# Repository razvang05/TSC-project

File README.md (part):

# TSC-project

**Author: Razvan Gheorghe 334CA**

## • Diagrama Bloc

## • BOM (Bill of Materials)

**Note:** TP-urile au fost construite de mine.

  | Nr. | Component Name | Procurement Link | Datasheet Link |
  |-----|----------------|------------------|----------------|
  | 1 | BOOT_BUTON | [Link](https://www.snapeda.com/parts/EVQP7L01P/Panasonic%20Electronic%20Components/view-part/?welcome=home) | [Datasheet](https://www.snapeda.com/parts/EVQP7L01P/Panasonic/datasheet/) |
  | 2 | C1 | [Link](https://componentsearchengine.com/part-view/CC0402MRX5R5BB106/YAGEO) | [Datasheet](https://componentsearchengine.com/Datasheets/2/CC0402MRX5R5BB106.pdf) |
  | 3 | C1_BAT | [Link](https://componentsearchengine.com/part-view/CC0402MRX5R5BB106/YAGEO) | [Datasheet](https://componentsearchengine.com/Datasheets/2/CC0402MRX5R5BB106.pdf) |
  | 4 | C1_BAT2 | [Link](https://componentsearchengine.com/part-view/CC0402MRX5R5BB106/YAGEO) | [Datasheet](https://componentsearchengine.com/Datasheets/2/CC0402MRX5R5BB106.pdf) |
  | 5 | C2 | [Link](https://componentsearchengine.com/part-view/CC0402MRX5R5BB106/YAGEO) | [Datasheet](https://componentsearchengine.com/Datasheets/2/CC0402MRX5R5BB106.pdf) |
  | 6 | C2_BAT | [Link](https://componentsearchengine.com/part-view/CC0402MRX5R5BB106/YAGEO) | [Datasheet](https://componentsearchengine.com/Datasheets/2/CC0402MRX5R5BB106.pdf) |
  | 7 | C3 | [Link](https://componentsearchengine.com/part-view/CC0402MRX5R5BB106/YAGEO) | [Datasheet](https://componentsearchengine.com/Datasheets/2/CC0402MRX5R5BB106.pdf) |
  | 8 | C4 | [Link](https://componentsearchengine.com/part-view/CC0402MRX5R5BB106/YAGEO) | [Datasheet](https://componentsearchengine.com/Datasheets/2/CC0402MRX5R5BB106.pdf) |
  | 9 | C4_USB | [Link](https://componentsearchengine.com/part-view/CC0402MRX5R5BB106/YAGEO) | [Datasheet](https://componentsearchengine.com/Datasheets/2/CC0402MRX5R5BB106.pdf) |
  | 10 | C5 | [Link](https://componentsearchengine.com/part-view/CC0402MRX5R5BB106/YAGEO) | [Datasheet](https://componentsearchengine.com/Datasheets/2/CC0402MRX5R5BB106.pdf) |
  | 11 | C5_USB | [Link](https://componentsearchengine.com/part-view/CC0402MRX5R5BB106/YAGEO) | [Datasheet](https://componentsearchengine.com/Datasheets/2/CC0402MRX5R5BB106.pdf) |
  | 12 | C6 | [Link](https://componentsearchengine.com/part-view/CC0402MRX5R5BB106/YAGEO) | [Datasheet](https://componentsearchengine.com/Datasheets/2/CC0402MRX5R5BB106.pdf) |
  | 13 | C7 | [Link](https://componentsearchengine.com/part-view/CC0402MRX5R5BB106/YAGEO) | [Datasheet](https://componentsearchengine.com/Datasheets/2/CC0402MRX5R5BB106.pdf) |
  | 14 | C8 | [Link](https://componentsearchengine.com/part-view/CC0402MRX5R5BB106/YAGEO) | [Datasheet](https://componentsearchengine.com/Datasheets/2/CC0402MRX5R5BB106.pdf) |
  | 15 | C9 | [Link](https://componentsearchengine.com/part-view/CC0402MRX5R5BB106/YAGEO) | [Datasheet](https://componentsearchengine.com/Datasheets/2/CC0402MRX5R5BB106.pdf) |
  | 16 | C10 | [Link](https://componentsearchengine.com/part-view/CC0402MRX5R5BB106/YAGEO) | [Datasheet](https://componentsearchengine.com/Datasheets/2/CC0402MRX5R5BB106.pdf) |
  | 17 | C10_SUPERCAR | [Link](https://industry.panasonic.com/global/en/products/control/switch/light-touch/number/evqpuj02k) | [Datasheet](https://industry.panasonic.com/global/en/downloads?tab=catalog&small_g_cd=203&part_no=EVQPUJ02K) |
  | 18 | CHANGE_BUTTON | [Link](https://www.snapeda.com/parts/EVQP7L01P/Panasonic%20Electronic%20Components/view-part/?welcome=home) | [Datasheet](https://www.snapeda.com/parts/EVQP7L01P/Panasonic/datasheet/) |
  | 19 | C_DELAY | [Link](https://componentsearchengine.com/part-view/CC0402MRX5R5BB106/YAGEO) | [Datasheet](https://componentsearchengine.com/Datasheets/2/CC0402MRX5R5BB106.pdf) |
  | 20 | D1 | [Link](https://www.snapeda.com/parts/USBLC6-2SC6Y/STMicroelectronics/view-part/?ref=eda) | [Datasheet](https://www.snapeda.com/parts/USBLC6-2SC6Y/STMicroelectronics/view-part/?ref=eda) |
  | 21 | D2 | [Link](https://ro.mouser.com/ProductDetail/KYOCERA-AVX/SD0805S020S1R0?qs=jCA%252BPfw4LHbpkAoSnwrdjw%3D%3D) | [Datasheet](https://ro.mouser.com/datasheet/2/40/schottky-3165252.pdf) |
  | 22 | D3 | [Link](https://ro.mouser.com/ProductDetail/KYOCERA-AVX/SD0805S020S1R0?qs=jCA%252BPfw4LHbpkAoSnwrdjw%3D%3D) | [Datasheet](https://ro.mouser.com/datasheet/2/40/schottky-3165252.pdf) |
  | 23 | D4 | [Link](https://ro.mouser.com/ProductDetail/KYOCERA-AVX/SD0805S020S1R0?qs=jCA%252BPfw4LHbpkAoSnwrdjw%3D%3D) | [Datasheet](https://ro.mouser.com/datasheet/2/40/schottky-3165252.pdf) |
  | 24 | D5 | [Link](https://ro.mouser.com/ProductDetail/KYOCERA-AVX/SD0805S020S1R0?qs=jCA%252BPfw4LHbpkAoSnwrdjw%3D%3D) | [Datasheet](https://ro.mouser.com/datasheet/2/40/schottky-3165252.pdf) |
  | 25 | D6 | [Link](https://www.snapeda.com/parts/PGB1010603MR/Littelfuse/view-part/?ref=eda) | [Datasheet](https://www.snapeda.com/parts/PGB1010603MR/Littelfuse%20Inc./datasheet/) |
  | 26 | D7 | [Link](https://ro.mouser.com/ProductDetail/KYOCERA-AVX/SD0805S020S1R0?qs=jCA%252BPfw4LHbpkAoSnwrdjw%3D%3D) | [Datasheet](https://ro.mouser.com/datasheet/2/40/schottky-3165252.pdf) |
  | 27 | D8 | [Link](https://www.snapeda.com/parts/PGB1010603MR/Littelfuse/view-part/?ref=eda) | [Datasheet](https://www.snapeda.com/parts/PGB1010603MR/Littelfuse%20Inc./datasheet/) |
  | 28 | D9 | [Link](https://www.snapeda.com/parts/PGB1010603MR/Littelfuse/view-part/?ref=eda) | [Datasheet](https://www.snapeda.com/parts/PGB1010603MR/Littelfuse%20Inc./datasheet/) |
  | 29 | D10 | [Link](https://www.snapeda.com/parts/PGB1010603MR/Littelfuse/view-part/?ref=eda) | [Datasheet](https://www.snapeda.com/parts/PGB1010603MR/Littelfuse%20Inc./datasheet/) |
  | 30 | D11 | [Link](https://www.snapeda.com/parts/PGB1010603MR/Littelfuse/view-part/?ref=eda) | [Datasheet](https://www.snapeda.com/parts/PGB1010603MR/Littelfuse%20Inc./datasheet/) |
  | 31 | D12 | [Link](https://www.snapeda.com/parts/PGB1010603MR/Littelfuse/view-part/?ref=eda) | [Datasheet](https://www.snapeda.com/parts/PGB1010603MR/Littelfuse%20Inc./datasheet/) |
  | 32 | EPD_C1 | [Link](https://componentsearchengine.com/part-view/CC0402MRX5R5BB106/YAGEO) | [Datasheet](https://componentsearchengine.com/Datasheets/2/CC0402MRX5R5BB106.pdf) |
  | 33 | EPD_C2 | [Link](https://componentsearchengine.com/part-view/CC0402MRX5R5BB106/YAGEO) | [Datasheet](https://componentsearchengine.com/Datasheets/2/CC0402MRX5R5BB106.pdf) |
  | 34 | EPD_C5 | [Link](https://componentsearchengine.com/part-view/CC0402MRX5R5BB106/YAGEO) | [Datasheet](https://componentsearchengine.com/Datasheets/2/CC0402MRX5R5BB106.pdf) |
  | 35 | EPD_C6 | [Link](https://componentsearchengine.com/part-view/CC0402MRX5R5BB106/YAGEO) | [Datasheet](https://componentsearchengine.com/Datasheets/2/CC0402MRX5R5BB106.pdf) |
  | 36 | EPD_C7 | [Link](https://componentsearchengine.com/part-view/CC0402MRX5R5BB106/YAGEO) | [Datasheet](https://componentsearchengine.com/Datasheets/2/CC0402MRX5R5BB106.pdf) |
  | 37 | EPD_C8 | [Link](https://componentsearchengine.com/part-view/CC0402MRX5R5BB106/YAGEO) | [Datasheet](https://componentsearchengine.com/Datasheets/2/CC0402MRX5R5BB106.pdf) |
  | 38 | EPD_C9 | [Link](https://componentsearchengine.com/part-view/CC0402MRX5R5BB106/YAGEO) | [Datasheet](https://componentsearchengine.com/Datasheets/2/CC0402MRX5R5BB106.pdf) |
  | 39 | EPD_C10 | [Link](https://componentsearchengine.com/part-view/CC0402MRX5R5BB106/YAGEO) | [Datasheet](https://componentsearchengine.com/Datasheets/2/CC0402MRX5R5BB106.pdf) |
  | 40 | EPD_C11 | [Link](https://componentsearchengine.com/part-view/CC0402MRX5R5BB106/YAGEO) | [Datasheet](https://componentsearchengine.com/Datasheets/2/CC0402MRX5R5BB106.pdf) |
  | 41 | EPD_C12 | [Link](https://componentsearchengine.com/part-view/CC0402MRX5R5BB106/YAGEO) | [Datasheet](https://componentsearchengine.com/Datasheets/2/CC0402MRX5R5BB106.pdf) |
  | 42 | IC1 | [Link](https://componentsearchengine.com/part-view/BD5229G-TR/ROHM%20Semiconductor) | [Datasheet](https://datasheet.datasheetarchive.com/originals/distributors/Datasheets_SAMA/f2b9741ef86007909f138d561a359946.pdf) |
  | 43 | IC4 | [Link](https://componentsearchengine.com/part-view/XC6220A331MR-G/Torex) | [Datasheet](https://product.torexsemi.com/system/files/series/xc6220.pdf) |
  | 44 | J1 | [Link](https://componentsearchengine.com/part-view/FH34SRJ-24S-0.5SH(99)/Hirose) | [Datasheet](https://www.hirose.com/en/product/document?clcode=CL0580-1255-6-99&productname=FH34SRJ-24S-0.5SH(99)&series=FH34SRJ&documenttype=2DDrawing&lang=en&documentid=0000990903) |
  | 45 | J2 | [Link](https://componentsearchengine.com/part-view/USB4110-GF-A/GCT%20(GLOBAL%20CONNECTOR%20TECHNOLOGY)) | [Datasheet](https://gct.co/files/drawings/usb4110.pdf) |
  | 46 | J3 | [Link](https://www.snapeda.com/parts/PRT-14417/SparkFun/view-part/) | [Datasheet](https://www.snapeda.com/parts/PRT-14417/SparkFun%20Electronics/datasheet/) |
  | 47 | J4 | [Link](https://www.snapeda.com/parts/112A-TAAR-R03/Attend/view-part/) | [Datasheet](https://www.snapeda.com/parts/112A-TAAR-R03/Attend/datasheet/) |
  | 48 | MCP73831 | [Link](https://ro.mouser.com/ProductDetail/Microchip-Technology/MCP73831T-2ACI-OT?qs=yUQqVecv4qvbBQBGbHx0Mw%3D%3D&utm_id=20109199409&utm_source=google&utm_medium=cpc&utm_marketing_tactic=emeacorp&gad_source=1&gbraid=0AAAAADn_wf0-USzm1eg1ywGvQg_qMgG3H) | [Datasheet](https://ro.mouser.com/datasheet/2/268/MCP73831_Family_Data_Sheet_DS20001984H-3441711.pdf) |
  | 49 | L1 | [Link](https://ro.mouser.com/ProductDetail/Wurth-Elektronik/744043680?qs=PGXP4M47uW6VkZq%252BkzjrHA%3D%3D) | [Datasheet](https://www.we-online.com/components/products/datasheet/744043680.pdf) |
  | 50 | PFMF.050.1 | [Link](https://ro.mouser.com/ProductDetail/EPCOS-TDK/B72520T0350K062?qs=dEfas%2FXlABIszF52uu7vrg%3D%3D) | [Datasheet](https://www.tdk-electronics.tdk.com/inf/75/db/CTVS_14/Surge_protection_series.pdf) |
  | 51 | Q1 | [Link](https://componentsearchengine.com/part-view/DMG2305UX-7/Diodes%20Incorporated) | [Datasheet](https://www.diodes.com//assets/Datasheets/DMG2305UX.pdf) |
  | 52 | Q2 | [Link](https://componentsearchengine.com/part-view/DMG2305UX-7/Diodes%20Incorporated) | [Datasheet](https://www.diodes.com//assets/Datasheets/DMG2305UX.pdf) |
  | 53 | Q3 | [Link](https://componentsearchengine.com/part-view/SI1308EDL-T1-GE3/Vishay) | [Datasheet](https://componentsearchengine.com/part-view/SI1308EDL-T1-GE3/Vishay) |
  | 54 | R1 | [Link](https://componentsearchengine.com/part-view/R0402%201%25%20100%20K%20(RC0402FR-07100KL)/YAGEO) | [Datasheet](https://www.yageo.com/upload/media/product/products/datasheet/rchip/PYu-RC_Group_51_RoHS_L_12.pdf) |
  | 55 | R1_PINH | [Link](https://componentsearchengine.com/part-view/R0402%201%25%20100%20K%20(RC0402FR-07100KL)/YAGEO) | [Datasheet](https://www.yageo.com/upload/media/product/products/datasheet/rchip/PYu-RC_Group_51_RoHS_L_12.pdf) |
  | 56 | R1_PINH1 | [Link](https://componentsearchengine.com/part-view/R0402%201%25%20100%20K%20(RC0402FR-07100KL)/YAGEO) | [Datasheet](https://www.yageo.com/upload/media/product/products/datasheet/rchip/PYu-RC_Group_51_RoHS_L_12.pdf) |
  | 57 | R1_BAT | [Link](https://componentsearchengine.com/part-view/R0402%201%25%20100%20K%20(RC0402FR-07100KL)/YAGEO) | [Datasheet](https://www.yageo.com/upload/media/product/products/datasheet/rchip/PYu-RC_Group_51_RoHS_L_12.pdf) |
  | 58 | R1_PWRUSB | [Link](https://componentsearchengine.com/part-view/R0402%201%25%20100%20K%20(RC0402FR-07100KL)/YAGEO) | [Datasheet](https://www.yageo.com/upload/media/product/products/datasheet/rchip/PYu-RC_Group_51_RoHS_L_12.pdf) |
  | 59 | R2 | [Link](https://componentsearchengine.com/part-view/R0402%201%25%20100%20K%20(RC0402FR-07100KL)/YAGEO) | [Datasheet](https://www.yageo.com/upload/media/product/products/datasheet/rchip/PYu-RC_Group_51_RoHS_L_12.pdf) |
  | 60 | R2_PINH | [Link](https://componentsearchengine.com/part-view/R0402%201%25%20100%20K%20(RC0402FR-07100KL)/YAGEO) | [Datasheet](https://www.yageo.com/upload/media/product/products/datasheet/rchip/PYu-RC_Group_51_RoHS_L_12.pdf) |
  | 61 | R2-PINH1 | [Link](https://componentsearchengine.com/part-view/R0402%201%25%20100%20K%20(RC0402FR-07100KL)/YAGEO) | [Datasheet](https://www.yageo.com/upload/media/product/products/datasheet/rchip/PYu-RC_Group_51_RoHS_L_12.pdf) |
  | 62 | R2 | [Link](https://componentsearchengine.com/part-view/R0402%201%25%20100%20K%20(RC0402FR-07100KL)/YAGEO) | [Datasheet](https://www.yageo.com/upload/media/product/products/datasheet/rchip/PYu-RC_Group_51_RoHS_L_12.pdf) |
  | 63 | R2-PINH | [Link](https://componentsearchengine.com/part-view/R0402%201%25%20100%20K%20(RC0402FR-07100KL)/YAGEO) | [Datasheet](https://www.yageo.com/upload/media/product/products/datasheet/rchip/PYu-RC_Group_51_RoHS_L_12.pdf) |
  | 64 | R2-PINH1 | [Link](https://componentsearchengine.com/part-view/R0402%201%25%20100%20K%20(RC0402FR-07100KL)/YAGEO) | [Datasheet](https://www.yageo.com/upload/media/product/products/datasheet/rchip/PYu-RC_Group_51_RoHS_L_12.pdf) |
  | 65 | R2_USB | [Link](https://componentsearchengine.com/part-view/R0402%201%25%20100%20K%20(RC0402FR-07100KL)/YAGEO) | [Datasheet](https://www.yageo.com/upload/media/product/products/datasheet/rchip/PYu-RC_Group_51_RoHS_L_12.pdf) |
  | 66 | R2_USB | [Link](https://componentsearchengine.com/part-view/R0402%201%25%20100%20K%20(RC0402FR-07100KL)/YAGEO) | [Datasheet](https://www.yageo.com/upload/media/product/products/datasheet/rchip/PYu-RC_Group_51_RoHS_L_12.pdf) |
  | 67 | R2_USB1 | [Link](https://componentsearchengine.com/part-view/R0402%201%25%20100%20K%20(RC0402FR-07100KL)/YAGEO) | [Datasheet](https://www.yageo.com/upload/media/product/products/datasheet/rchip/PYu-RC_Group_51_RoHS_L_12.pdf) |
  | 68 | R3 | [Link](https://componentsearchengine.com/part-view/R0402%201%25%20100%20K%20(RC0402FR-07100KL)/YAGEO) | [Datasheet](https://www.yageo.com/upload/media/product/products/datasheet/rchip/PYu-RC_Group_51_RoHS_L_12.pdf) |
  | 69 | R4 | [Link](https://componentsearchengine.com/part-view/R0402%201%25%20100%20K%20(RC0402FR-07100KL)/YAGEO) | [Datasheet](https://www.yageo.com/upload/media/product/products/datasheet/rchip/PYu-RC_Group_51_RoHS_L_12.pdf) |
  | 70 | R5 | [Link](https://componentsearchengine.com/part-view/R0402%201%25%20100%20K%20(RC0402FR-07100KL)/YAGEO) | [Datasheet](https://www.yageo.com/upload/media/product/products/datasheet/rchip/PYu-RC_Group_51_RoHS_L_12.pdf) |
  | 71 | R6 | [Link](https://componentsearchengine.com/part-view/R0402%201%25%20100%20K%20(RC0402FR-07100KL)/YAGEO) | [Datasheet](https://www.yageo.com/upload/media/product/products/datasheet/rchip/PYu-RC_Group_51_RoHS_L_12.pdf) |
  | 72 | R7 | [Link](https://componentsearchengine.com/part-view/R0402%201%25%20100%20K%20(RC0402FR-07100KL)/YAGEO) | [Datasheet](https://www.yageo.com/upload/media/product/products/datasheet/rchip/PYu-RC_Group_51_RoHS_L_12.pdf) |
  | 73 | R8 | [Link](https://componentsearchengine.com/part-view/R0402%201%25%20100%20K%20(RC0402FR-07100KL)/YAGEO) | [Datasheet](https://www.yageo.com/upload/media/product/products/datasheet/rchip/PYu-RC_Group_51_RoHS_L_12.pdf) |
  | 74 | R9 | [Link](https://componentsearchengine.com/part-view/R0402%201%25%20100%20K%20(RC0402FR-07100KL)/YAGEO) | [Datasheet](https://www.yageo.com/upload/media/product/products/datasheet/rchip/PYu-RC_Group_51_RoHS_L_12.pdf) |
  | 75 | R10 | [Link](https://componentsearchengine.com/part-view/R0402%201%25%20100%20K%20(RC0402FR-07100KL)/YAGEO) | [Datasheet](https://www.yageo.com/upload/media/product/products/datasheet/rchip/PYu-RC_Group_51_RoHS_L_12.pdf) |
  | 76 | RESET_BUTTON | [Link](https://www.snapeda.com/parts/EVQP7L01P/Panasonic%20Electronic%20Components/view-part/?welcome=home) | [Datasheet](https://www.snapeda.com/parts/EVQP7L01P/Panasonic/datasheet/) |
  | 77 | R_BOOT | [Link](https://componentsearchengine.com/part-view/R0402%201%25%20100%20K%20(RC0402FR-07100KL)/YAGEO) | [Datasheet](https://www.yageo.com/upload/media/product/products/datasheet/rchip/PYu-RC_Group_51_RoHS_L_12.pdf) |
  | 78 | R_CAPACITOR | [Link](https://componentsearchengine.com/part-view/R0402%201%25%20100%20K%20(RC0402FR-07100KL)/YAGEO) | [Datasheet](https://www.yageo.com/upload/media/product/products/datasheet/rchip/PYu-RC_Group_51_RoHS_L_12.pdf) |
  | 79 | R_CHANGE | [Link](https://componentsearchengine.com/part-view/R0402%201%25%20100%20K%20(RC0402FR-07100KL)/YAGEO) | [Datasheet](https://www.yageo.com/upload/media/product/products/datasheet/rchip/PYu-RC_Group_51_RoHS_L_12.pdf) |
  | 80 | R_CL1 | [Link](https://componentsearchengine.com/part-view/R0402%201%25%20100%20K%20(RC0402FR-07100KL)/YAGEO) | [Datasheet](https://www.yageo.com/upload/media/product/products/datasheet/rchip/PYu-RC_Group_51_RoHS_L_12.pdf) |
  | 81 | R_RESET | [Link](https://componentsearchengine.com/part-view/R0402%201%25%20100%20K%20(RC0402FR-07100KL)/YAGEO) | [Datasheet](https://www.yageo.com/upload/media/product/products/datasheet/rchip/PYu-RC_Group_51_RoHS_L_12.pdf) |
  | 82 | SENSOR2 | [Link](https://www.snapeda.com/parts/BME680/Bosch/view-part/?welcome=home) | [Datasheet](https://www.snapeda.com/parts/BME680/Bosch%20Sensortec/datasheet/) |
  | 83 | SJ1 | [Link](https://grabcad.com/library/solder-jumpers-1) | [Datasheet](https://grabcad.com/library/solder-jumpers-1) |
  | 84 | TP1 | [Link](nan) | [Datasheet](nan) |
  | 85 | TP2 | [Link](nan) | [Datasheet](nan) |
  | 86 | TP3 | [Link](nan) | [Datasheet](nan) |
  | 87 | TP4 | [Link](nan) | [Datasheet](nan) |
  | 88 | TP5 | [Link](nan) | [Datasheet](nan) |
  | 89 | TP6 | [Link](nan) | [Datasheet](nan) |
  | 90 | TP7 | [Link](nan) | [Datasheet](nan) |
  | 91 | TP8 | [Link](nan) | [Datasheet](nan) |
  | 92 | TP9 | [Link](nan) | [Datasheet](nan) |
  | 93 | TP10 | [Link](nan) | [Datasheet](nan) |
  | 94 | TP11 | [Link](nan) | [Datasheet](nan) |
  | 95 | TP12 | [Link](nan) | [Datasheet](nan) |
  | 96 | TP13 | [Link](nan) | [Datasheet](nan) |
  | 97 | TP14 | [Link](nan) | [Datasheet](nan) |
  | 98 | TP15 | [Link](nan) | [Datasheet](nan) |
  | 99 | TP16 | [Link](nan) | [Datasheet](nan) |
  | 100 | TP17 | [Link](nan) | [Datasheet](nan) |
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
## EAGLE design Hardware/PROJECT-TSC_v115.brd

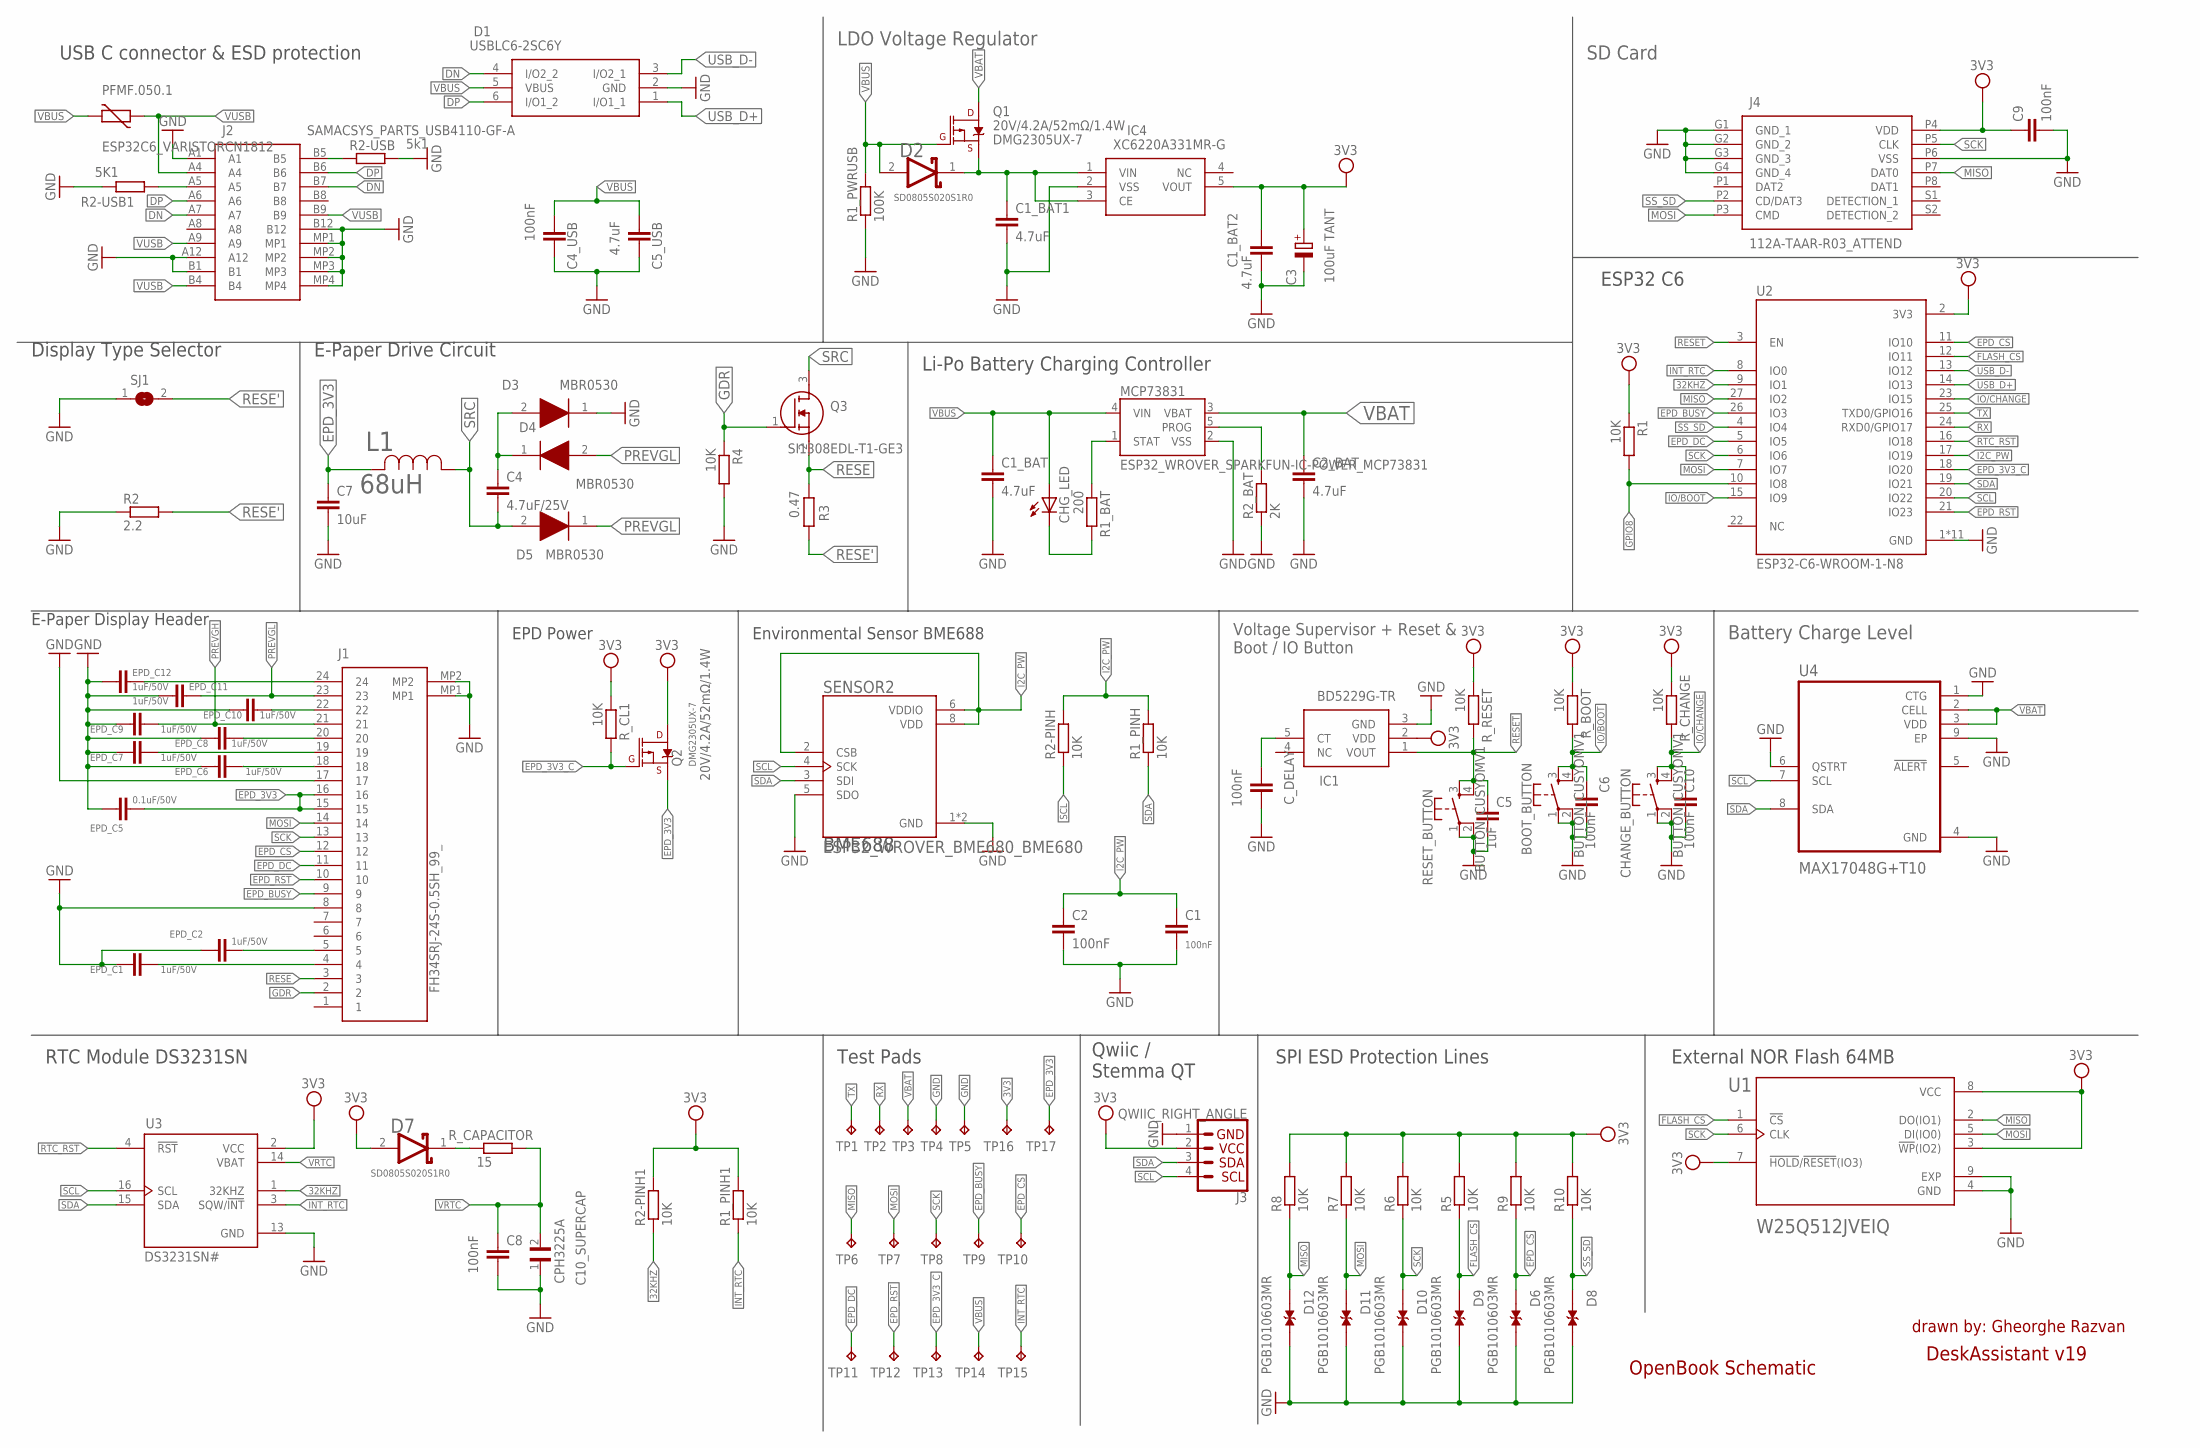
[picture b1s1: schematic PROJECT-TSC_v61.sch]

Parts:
BOOT_BUTTON: BUTTON_CUSYOMV1; MYBUTTON
C1, C2, C4_USB, C6, C8, C9, C10: 100nF; EAGLE-LTSPICE_C0402
C1_BAT, C1_BAT1, C1_BAT2, C2_BAT, C5_USB: 4.7uF; EAGLE-LTSPICE_C0402
C3: 100uF TANT; RCL_CT3528
C4: 4.7uF/25V; EAGLE-LTSPICE_C0402
C5: 1uF; EAGLE-LTSPICE_C0402
C7: 10uF; EAGLE-LTSPICE_C0402
C10_SUPERCAP: CPH3225A; CAPCP3225X100N
CHANGE_BUTTON: BUTTON_CUSYOMV1; MYBUTTON
CHG_LED: ADAFRUIT_LEDCHIP-LED0603; ADAFRUIT_CHIP-LED0603
C_DELAY: 100nF; EAGLE-LTSPICE_C0402
D1: USBLC6-2SC6Y; SOT95P280X145-6N
D2, D7: ESP32_WROVER_AVX---SD0805S020S1R0_AVX_SD0805S020S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; ESP32_WROVER_AVX---SD0805S020S1R0_AVX_SD0805S020S1R0_0
D3, D4, D5: MBR0530; SOD3716X135N
D6, D8, D9, D10, D11, D12: PGB1010603MR; DIOC1608X36N
EPD_C1, EPD_C2, EPD_C6, EPD_C7, EPD_C8, EPD_C9, EPD_C10, EPD_C11, EPD_C12: 1uF/50V; EAGLE-LTSPICE_C0402
EPD_C5: 0.1uF/50V; EAGLE-LTSPICE_C0402
IC1: BD5229G-TR; SOT95P280X120-5N
IC4: XC6220A331MR-G; SOT95P280X120-5N
J1: FH34SRJ-24S-0.5SH_99_; FH34SRJ24S05SH99
J2: SAMACSYS_PARTS_USB4110-GF-A; SAMACSYS_PARTS_USB4110GFA
J3: QWIIC_RIGHT_ANGLE; JST04_1MM_RA
J4: 112A-TAAR-R03_ATTEND; 112ATAARR03ATTEND
L1: 68uH; IND_4828-WE-TPC_WRE
MCP73831: ESP32_WROVER_SPARKFUN-IC-POWER_MCP73831; ESP32_WROVER_SPARKFUN-IC-POWER_SOT23-5
PFMF.050.1: ESP32C6_VARISTORCN1812; ESP32C6_VARISTOR_CT/CN1812
Q1, Q2: 20V/4.2A/52mΩ/1.4W; ESP32_WROVER_SPARKFUN-DISCRETESEMI_SOT23-3
Q3: SI1308EDL-T1-GE3; SOT65P210X110-3N
R1, R1_PINH, R1_PINH1, R2-PINH, R2-PINH1, R4, R5, R6, R7, R8, R9, R10: 10K; ESP32_WROVER_EAGLE-LTSPICE_R0402
R1_BAT: 200; ESP32_WROVER_EAGLE-LTSPICE_R0402
R1_PWRUSB: 100K; ESP32_WROVER_EAGLE-LTSPICE_R0402
R2: 2.2; ESP32_WROVER_EAGLE-LTSPICE_R0402
R2-USB: 5k1; ESP32_WROVER_EAGLE-LTSPICE_R0402
R2-USB1: 5K1; ESP32_WROVER_EAGLE-LTSPICE_R0402
R2_BAT: 2K; ESP32_WROVER_EAGLE-LTSPICE_R0402
R3: 0.47; ESP32_WROVER_EAGLE-LTSPICE_R0402
RESET_BUTTON: BUTTON_CUSYOMV1; MYBUTTON
R_BOOT: 10K; ESP32_WROVER_EAGLE-LTSPICE_R0402
R_CAPACITOR: 15; ESP32_WROVER_EAGLE-LTSPICE_R0402
R_CHANGE: 10K; ESP32_WROVER_EAGLE-LTSPICE_R0402
R_CL1: 10K; ESP32_WROVER_EAGLE-LTSPICE_R0402
R_RESET: 10K; ESP32_WROVER_EAGLE-LTSPICE_R0402
SENSOR2: ESP32_WROVER_BME680_BME680; ESP32_WROVER_BME680_PSON80P300X300X100-8N
SJ1: SJ
TP1, TP2, TP3, TP4, TP5, TP6, TP7, TP8, TP9, TP10, TP11, TP12, TP13, TP14, TP15, TP16, TP17: TPTP20R; TP20R
U1: W25Q512JVEIQ; SON127P600X800X80-9N
U2: ESP32-C6-WROOM-1-N8; XCVR_ESP32-C6-WROOM-1-N8
U3: DS3231SN#; SOIC127P1032X265-16N
U4: MAX17048G+T10; SON50P200X200X80-9N

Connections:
3V3: C1_BAT2.1, C3.+, C9.1, D7.2 (ANODE), IC1.2 (VDD), IC4.5 (VOUT), J3.2, J4.P4 (VDD), Q2.3 (D), R1.1, R1_PINH1.2, R2-PINH1.2, R5.2, R6.2, R7.2, R8.2, R9.2, R10.2, R_BOOT.1, R_CHANGE.1, R_CL1.1, R_RESET.1, TP16.TP, U1.3 (!WP!(IO2)), U1.7 (!HOLD!/!RESET!(IO3)), U1.8 (VCC), U2.2 (3V3), U3.2 (VCC)
32KHZ: R2-PINH1.1, U2.9 (IO1), U3.1 (32KHZ)
DN: D1.4 (I/O2_2), J2.A7, J2.B7
DP: D1.6 (I/O1_2), J2.A6, J2.B6
EPD_3V3: C7.1, EPD_C5.1, J1.15, J1.16, L1.2, Q2.2 (S), TP17.TP
EPD_3V3_C: Q2.1 (G), R_CL1.2, TP13.TP, U2.18 (IO20)
EPD_BUSY: J1.9, TP9.TP, U2.26 (IO3)
EPD_CS: D6.1, J1.12, R9.1, TP10.TP, U2.11 (IO10)
EPD_DC: J1.11, TP11.TP, U2.5 (IO5)
EPD_RST: J1.10, TP12.TP, U2.21 (IO23)
FLASH_CS: D9.1, R5.1, U1.1 (!CS), U2.12 (IO11)
GDR: J1.2, Q3.1 (G), R4.1
GND: BOOT_BUTTON.1, BOOT_BUTTON.2, C1.2, C1_BAT.2, C1_BAT1.2, C1_BAT2.2, C2.2, C2_BAT.2, C3.-, C4_USB.2, C5.2, C5_USB.2, C6.2, C7.2, C8.2, C9.2, C10.2, C10_SUPERCAP.1, CHANGE_BUTTON.1, CHANGE_BUTTON.2, C_DELAY.2, D1.2 (GND), D3.1 (K), D6.2, D8.2, D9.2, D10.2, D11.2, D12.2, EPD_C1.2, EPD_C2.2, EPD_C5.2, EPD_C6.2, EPD_C7.2, EPD_C8.2, EPD_C9.2, EPD_C10.2, EPD_C11.2, EPD_C12.2, IC1.3 (GND), IC4.2 (VSS), J1.8, J1.17, J1.MP1, J1.MP2, J2.A1, J2.A12, J2.B1, J2.B12, J2.MP1, J2.MP2, J2.MP3, J2.MP4, J3.1, J4.G1 (GND_1), J4.G2 (GND_2), J4.G3 (GND_3), J4.G4 (GND_4), J4.P6 (VSS), MCP73831.2 (VSS), R1_PWRUSB.1, R2.1, R2-USB.2, R2-USB1.1, R2_BAT.1, R4.2, RESET_BUTTON.1, RESET_BUTTON.2, SENSOR2.1 (GND), SENSOR2.5 (SDO), SENSOR2.7 (GND), SJ1.1, TP4.TP, TP5.TP, U1.4 (GND), U1.9 (EXP), U2.1 (GND), U2.28 (GND), U2.29_1 (GND), U2.29_2 (GND), U2.29_3 (GND), U2.29_4 (GND), U2.29_5 (GND), U2.29_6 (GND), U2.29_7 (GND), U2.29_8 (GND), U2.29_9 (GND), U3.13 (GND), U4.1 (CTG), U4.4 (GND), U4.6 (QSTRT), U4.9 (EP)
GPIO8: R1.2, U2.10 (IO8)
I2C_PW: C1.1, C2.1, R1_PINH.2, R2-PINH.2, SENSOR2.2 (CSB), SENSOR2.6 (VDDIO), SENSOR2.8 (VDD), U2.17 (IO19)
INT_RTC: R1_PINH1.1, TP15.TP, U2.8 (IO0), U3.3 (SQW/!INT)
IO/BOOT: BOOT_BUTTON.3, BOOT_BUTTON.4, C6.1, R_BOOT.2, U2.15 (IO9)
IO/CHANGE: C10.1, CHANGE_BUTTON.3, CHANGE_BUTTON.4, R_CHANGE.2, U2.23 (IO15)
MISO: D12.1, J4.P7 (DAT0), R8.1, TP6.TP, U1.2 (DO(IO1)), U2.27 (IO2)
MOSI: D11.1, J1.14, J4.P3 (CMD), R7.1, TP7.TP, U1.5 (DI(IO0)), U2.7 (IO7)
unnamed: J2.A5, R2-USB1.2
unnamed: J2.B5, R2-USB.1
unnamed: C1_BAT1.1, D2.1 (CATHODE), IC4.1 (VIN), IC4.3 (CE), Q1.2 (S)
unnamed: C4.1, D3.2 (A), D4.1 (K)
unnamed: C_DELAY.1, IC1.5 (CT)
unnamed: CHG_LED.C, R1_BAT.2
unnamed: MCP73831.1 (STAT), R1_BAT.1
unnamed: EPD_C1.1, J1.4
unnamed: MCP73831.5 (PROG), R2_BAT.2
unnamed: EPD_C2.1, J1.5
unnamed: D7.1 (CATHODE), R_CAPACITOR.1
unnamed: EPD_C8.1, J1.20
unnamed: EPD_C7.1, J1.19
unnamed: EPD_C6.1, J1.18
unnamed: EPD_C10.1, J1.22
unnamed: EPD_C12.1, J1.24
PREVGH: EPD_C9.1, J1.21
PREVGL: D4.2 (A), D5.1 (K), EPD_C11.1, J1.23
RESE: J1.3, Q3.2 (S), R3.1
RESE': R2.2, R3.2, SJ1.2
RESET: C5.1, IC1.1 (VOUT), RESET_BUTTON.3, RESET_BUTTON.4, R_RESET.2, U2.3 (EN)
RTC_RST: U2.16 (IO18), U3.4 (!RST)
RX: TP2.TP, U2.24 (RXD0/GPIO17)
SCK: D10.1, J1.13, J4.P5 (CLK), R6.1, TP8.TP, U1.6 (CLK), U2.6 (IO6)
SCL: J3.4, R2-PINH.1, SENSOR2.4 (SCK), U2.20 (IO22), U3.16 (SCL), U4.7 (SCL)
SDA: J3.3, R1_PINH.1, SENSOR2.3 (SDI), U2.19 (IO21), U3.15 (SDA), U4.8 (SDA)
SRC: C4.2, D5.2 (A), L1.1, Q3.3 (D)
SS_SD: D8.1, J4.P2 (CD/DAT3), R10.1, U2.4 (IO4)
TX: TP1.TP, U2.25 (TXD0/GPIO16)
USB_D+: D1.1 (I/O1_1), U2.14 (IO13)
USB_D-: D1.3 (I/O2_1), U2.13 (IO12)
VBAT: C2_BAT.1, MCP73831.3 (VBAT), Q1.3 (D), TP3.TP, U4.2 (CELL), U4.3 (VDD)
VBUS: C1_BAT.1, C4_USB.1, C5_USB.1, CHG_LED.A, D1.5 (VBUS), D2.2 (ANODE), MCP73831.4 (VIN), PFMF.050.1.2, Q1.1 (G), R1_PWRUSB.2, TP14.TP
VRTC: C8.1, C10_SUPERCAP.2, R_CAPACITOR.2, U3.14 (VBAT)
VUSB: J2.A4, J2.A9, J2.B4, J2.B9, PFMF.050.1.1

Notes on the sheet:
USB C connector & ESD protection
LDO Voltage Regulator
SD Card
Display Type Selector
E-Paper Drive Circuit
Li-Po Battery Charging Controller
ESP32 C6
E-Paper Display Header
EPD Power
Environmental Sensor BME688
BME688
RTC Module DS3231SN
Test Pads
Qwiic / Stemma QT
SPI ESD Protection Lines
External NOR Flash 64MB
Battery Charge Level
Voltage Supervisor + Reset & Boot / IO Button
OpenBook Schematic
drawn by: Gheorghe Razvan
DeskAssistant v19
DMG2305UX-7
SD0805S020S1R0

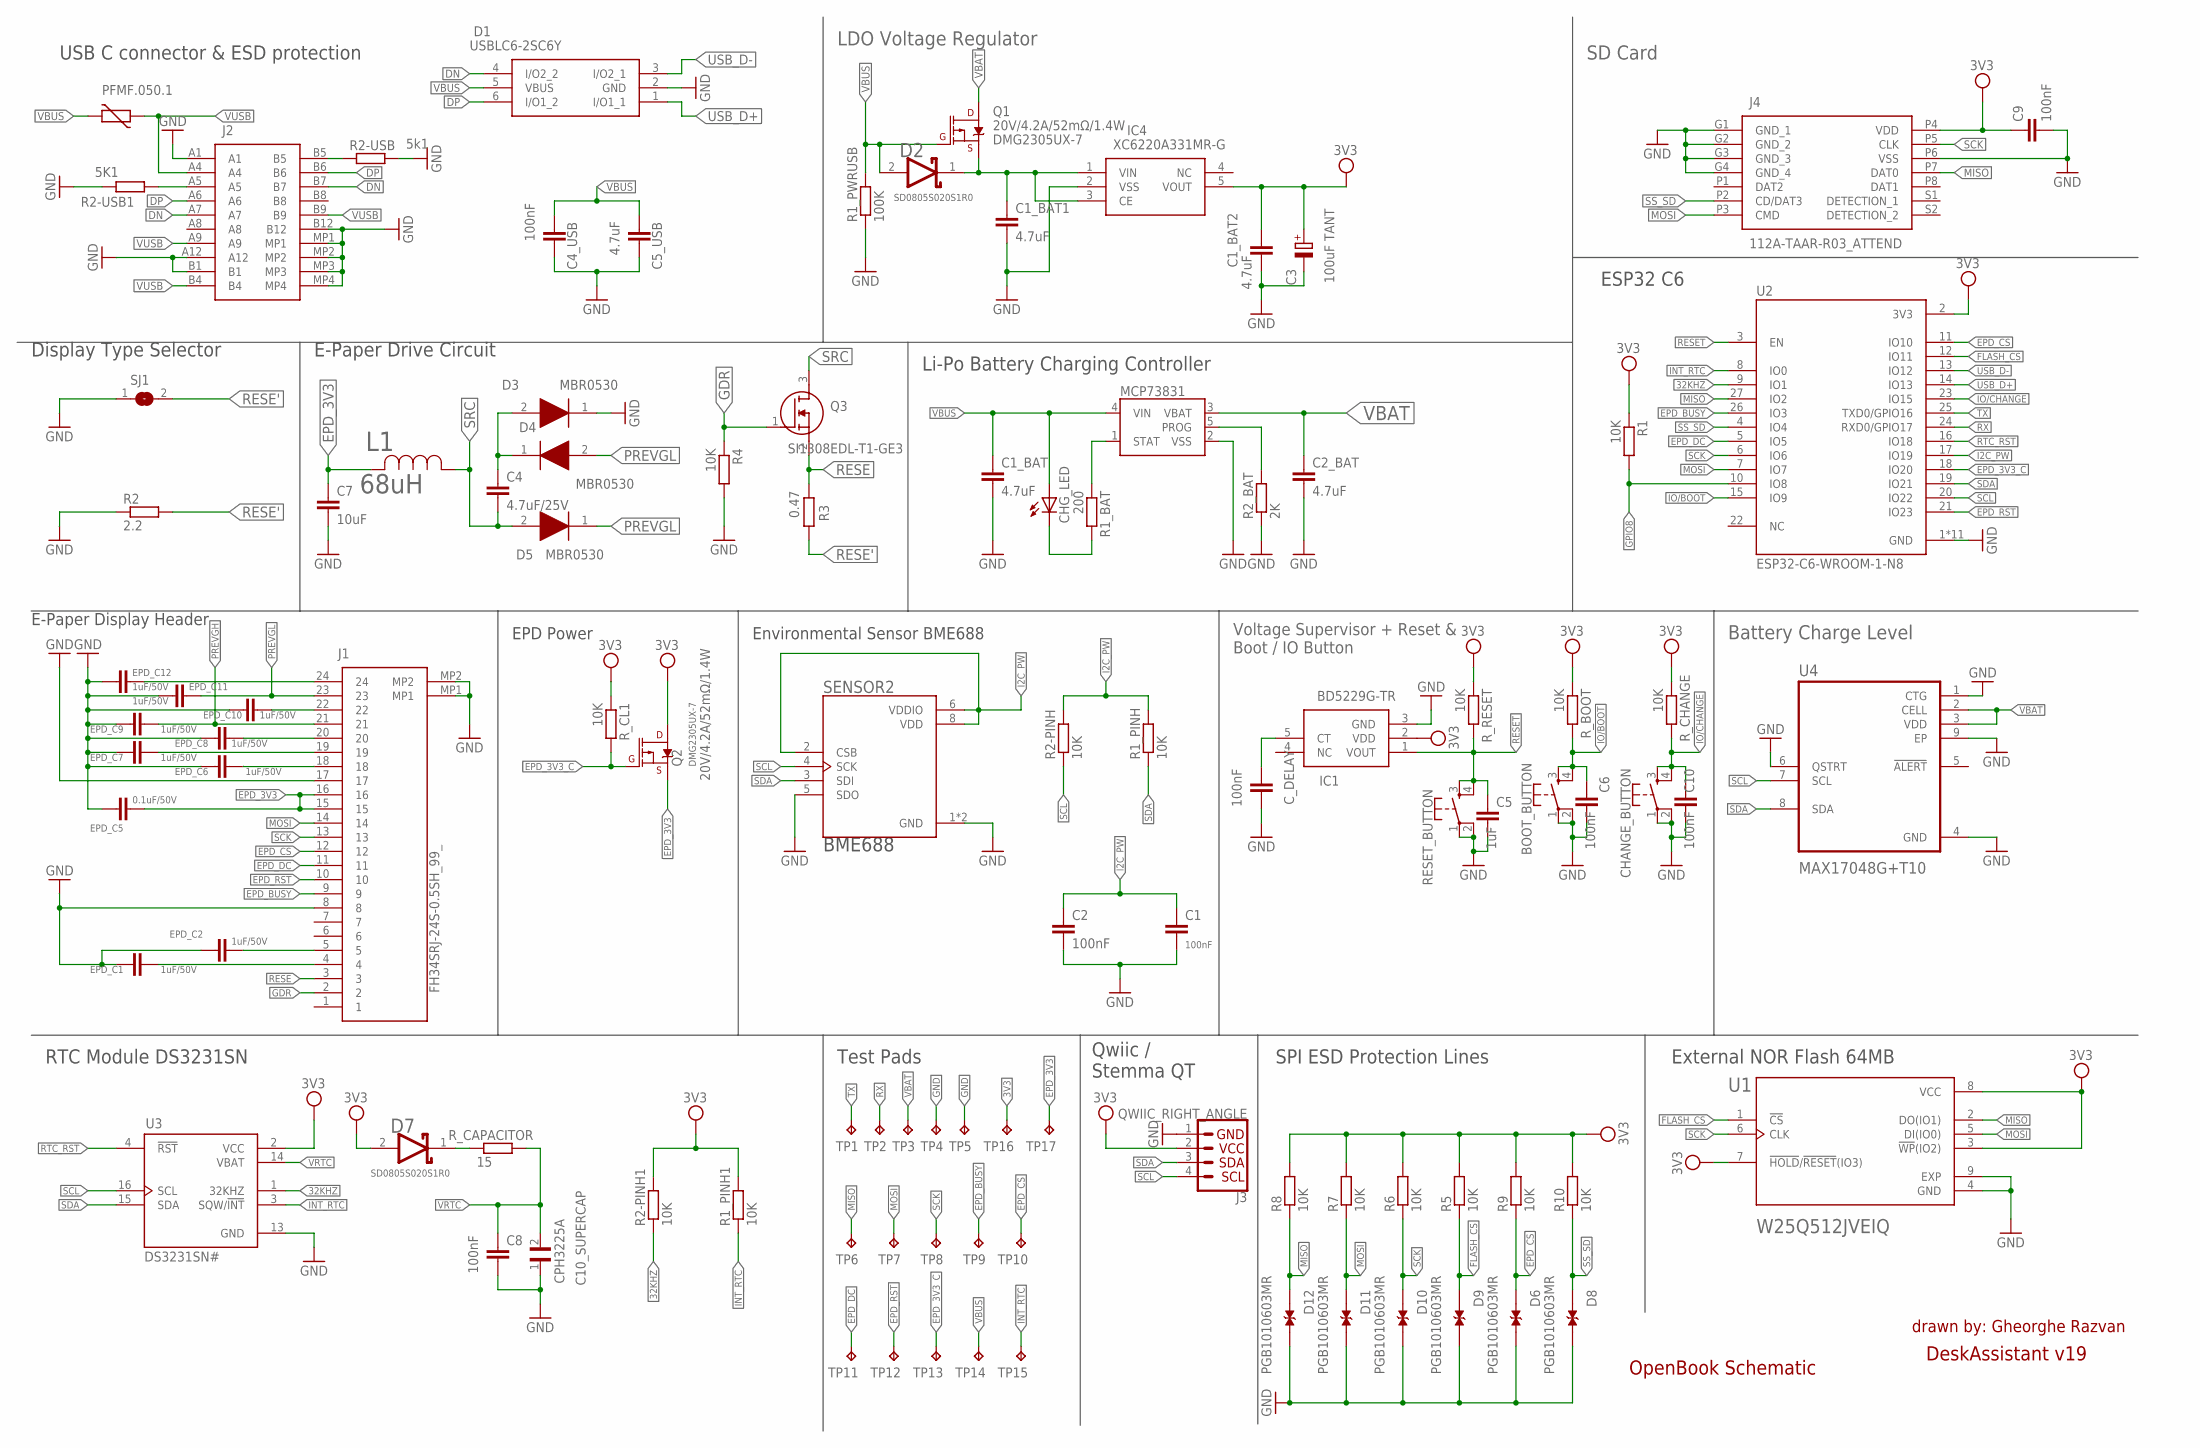
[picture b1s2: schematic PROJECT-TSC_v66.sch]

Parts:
BOOT_BUTTON: BUTTON_CUSYOMV1; MYBUTTON
C1, C2, C4_USB, C6, C8, C9, C10: 100nF; EAGLE-LTSPICE_C0402
C1_BAT, C1_BAT1, C1_BAT2, C2_BAT, C5_USB: 4.7uF; EAGLE-LTSPICE_C0402
C3: 100uF TANT; RCL_CT3528
C4: 4.7uF/25V; EAGLE-LTSPICE_C0402
C5: 1uF; EAGLE-LTSPICE_C0402
C7: 10uF; EAGLE-LTSPICE_C0402
C10_SUPERCAP: CPH3225A; CAPCP3225X100N
CHANGE_BUTTON: BUTTON_CUSYOMV1; MYBUTTON
CHG_LED: ADAFRUIT_LEDCHIP-LED0603; ADAFRUIT_CHIP-LED0603
C_DELAY: 100nF; EAGLE-LTSPICE_C0402
D1: USBLC6-2SC6Y; SOT95P280X145-6N
D2, D7: ESP32_WROVER_AVX---SD0805S020S1R0_AVX_SD0805S020S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; ESP32_WROVER_AVX---SD0805S020S1R0_AVX_SD0805S020S1R0_0
D3, D4, D5: MBR0530; SOD3716X135N
D6, D8, D9, D10, D11, D12: PGB1010603MR; DIOC1608X36N
EPD_C1, EPD_C2, EPD_C6, EPD_C7, EPD_C8, EPD_C9, EPD_C10, EPD_C11, EPD_C12: 1uF/50V; EAGLE-LTSPICE_C0402
EPD_C5: 0.1uF/50V; EAGLE-LTSPICE_C0402
IC1: BD5229G-TR; SOT95P280X120-5N
IC4: XC6220A331MR-G; SOT95P280X120-5N
J1: FH34SRJ-24S-0.5SH_99_; FH34SRJ24S05SH99
J2: SAMACSYS_PARTS_USB4110-GF-A; SAMACSYS_PARTS_USB4110GFA
J3: QWIIC_RIGHT_ANGLE; JST04_1MM_RA
J4: 112A-TAAR-R03_ATTEND; 112ATAARR03ATTEND
L1: 68uH; IND_4828-WE-TPC_WRE
MCP73831: ESP32_WROVER_SPARKFUN-IC-POWER_MCP73831; ESP32_WROVER_SPARKFUN-IC-POWER_SOT23-5
PFMF.050.1: ESP32C6_VARISTORCN1812; ESP32C6_VARISTOR_CT/CN1812
Q1, Q2: 20V/4.2A/52mΩ/1.4W; ESP32_WROVER_SPARKFUN-DISCRETESEMI_SOT23-3
Q3: SI1308EDL-T1-GE3; SOT65P210X110-3N
R1, R1_PINH, R1_PINH1, R2-PINH, R2-PINH1, R4, R5, R6, R7, R8, R9, R10: 10K; ESP32_WROVER_EAGLE-LTSPICE_R0402
R1_BAT: 200; ESP32_WROVER_EAGLE-LTSPICE_R0402
R1_PWRUSB: 100K; ESP32_WROVER_EAGLE-LTSPICE_R0402
R2: 2.2; ESP32_WROVER_EAGLE-LTSPICE_R0402
R2-USB: 5k1; ESP32_WROVER_EAGLE-LTSPICE_R0402
R2-USB1: 5K1; ESP32_WROVER_EAGLE-LTSPICE_R0402
R2_BAT: 2K; ESP32_WROVER_EAGLE-LTSPICE_R0402
R3: 0.47; ESP32_WROVER_EAGLE-LTSPICE_R0402
RESET_BUTTON: BUTTON_CUSYOMV1; MYBUTTON
R_BOOT: 10K; ESP32_WROVER_EAGLE-LTSPICE_R0402
R_CAPACITOR: 15; ESP32_WROVER_EAGLE-LTSPICE_R0402
R_CHANGE: 10K; ESP32_WROVER_EAGLE-LTSPICE_R0402
R_CL1: 10K; ESP32_WROVER_EAGLE-LTSPICE_R0402
R_RESET: 10K; ESP32_WROVER_EAGLE-LTSPICE_R0402
SENSOR2: ESP32_WROVER_BME680_BME680; ESP32_WROVER_BME680_PSON80P300X300X100-8N
SJ1: SJ
TP1, TP2, TP3, TP4, TP5, TP6, TP7, TP8, TP9, TP10, TP11, TP12, TP13, TP14, TP15, TP16, TP17: TPTP20R; TP20R
U1: W25Q512JVEIQ; SON127P600X800X80-9N
U2: ESP32-C6-WROOM-1-N8; XCVR_ESP32-C6-WROOM-1-N8
U3: DS3231SN#; SOIC127P1032X265-16N
U4: MAX17048G+T10; SON50P200X200X80-9N

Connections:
3V3: C1_BAT2.1, C3.+, C9.1, D7.2 (ANODE), IC1.2 (VDD), IC4.5 (VOUT), J3.2, J4.P4 (VDD), Q2.3 (D), R1.1, R1_PINH1.2, R2-PINH1.2, R5.2, R6.2, R7.2, R8.2, R9.2, R10.2, R_BOOT.1, R_CHANGE.1, R_CL1.1, R_RESET.1, TP16.TP, U1.3 (!WP!(IO2)), U1.7 (!HOLD!/!RESET!(IO3)), U1.8 (VCC), U2.2 (3V3), U3.2 (VCC)
32KHZ: R2-PINH1.1, U2.9 (IO1), U3.1 (32KHZ)
DN: D1.4 (I/O2_2), J2.A7, J2.B7
DP: D1.6 (I/O1_2), J2.A6, J2.B6
EPD_3V3: C7.1, EPD_C5.1, J1.15, J1.16, L1.2, Q2.2 (S), TP17.TP
EPD_3V3_C: Q2.1 (G), R_CL1.2, TP13.TP, U2.18 (IO20)
EPD_BUSY: J1.9, TP9.TP, U2.26 (IO3)
EPD_CS: D6.1, J1.12, R9.1, TP10.TP, U2.11 (IO10)
EPD_DC: J1.11, TP11.TP, U2.5 (IO5)
EPD_RST: J1.10, TP12.TP, U2.21 (IO23)
FLASH_CS: D9.1, R5.1, U1.1 (!CS), U2.12 (IO11)
GDR: J1.2, Q3.1 (G), R4.1
GND: BOOT_BUTTON.1, BOOT_BUTTON.2, C1.2, C1_BAT.2, C1_BAT1.2, C1_BAT2.2, C2.2, C2_BAT.2, C3.-, C4_USB.2, C5.2, C5_USB.2, C6.2, C7.2, C8.2, C9.2, C10.2, C10_SUPERCAP.1, CHANGE_BUTTON.1, CHANGE_BUTTON.2, C_DELAY.2, D1.2 (GND), D3.1 (K), D6.2, D8.2, D9.2, D10.2, D11.2, D12.2, EPD_C1.2, EPD_C2.2, EPD_C5.2, EPD_C6.2, EPD_C7.2, EPD_C8.2, EPD_C9.2, EPD_C10.2, EPD_C11.2, EPD_C12.2, IC1.3 (GND), IC4.2 (VSS), J1.8, J1.17, J1.MP1, J1.MP2, J2.A1, J2.A12, J2.B1, J2.B12, J2.MP1, J2.MP2, J2.MP3, J2.MP4, J3.1, J4.G1 (GND_1), J4.G2 (GND_2), J4.G3 (GND_3), J4.G4 (GND_4), J4.P6 (VSS), MCP73831.2 (VSS), R1_PWRUSB.1, R2.1, R2-USB.2, R2-USB1.1, R2_BAT.1, R4.2, RESET_BUTTON.1, RESET_BUTTON.2, SENSOR2.1 (GND), SENSOR2.5 (SDO), SENSOR2.7 (GND), SJ1.1, TP4.TP, TP5.TP, U1.4 (GND), U1.9 (EXP), U2.1 (GND), U2.28 (GND), U2.29_1 (GND), U2.29_2 (GND), U2.29_3 (GND), U2.29_4 (GND), U2.29_5 (GND), U2.29_6 (GND), U2.29_7 (GND), U2.29_8 (GND), U2.29_9 (GND), U3.13 (GND), U4.1 (CTG), U4.4 (GND), U4.6 (QSTRT), U4.9 (EP)
GPIO8: R1.2, U2.10 (IO8)
I2C_PW: C1.1, C2.1, R1_PINH.2, R2-PINH.2, SENSOR2.2 (CSB), SENSOR2.6 (VDDIO), SENSOR2.8 (VDD), U2.17 (IO19)
INT_RTC: R1_PINH1.1, TP15.TP, U2.8 (IO0), U3.3 (SQW/!INT)
IO/BOOT: BOOT_BUTTON.3, BOOT_BUTTON.4, C6.1, R_BOOT.2, U2.15 (IO9)
IO/CHANGE: C10.1, CHANGE_BUTTON.3, CHANGE_BUTTON.4, R_CHANGE.2, U2.23 (IO15)
MISO: D12.1, J4.P7 (DAT0), R8.1, TP6.TP, U1.2 (DO(IO1)), U2.27 (IO2)
MOSI: D11.1, J1.14, J4.P3 (CMD), R7.1, TP7.TP, U1.5 (DI(IO0)), U2.7 (IO7)
unnamed: J2.A5, R2-USB1.2
unnamed: J2.B5, R2-USB.1
unnamed: C1_BAT1.1, D2.1 (CATHODE), IC4.1 (VIN), IC4.3 (CE), Q1.2 (S)
unnamed: C4.1, D3.2 (A), D4.1 (K)
unnamed: C_DELAY.1, IC1.5 (CT)
unnamed: CHG_LED.C, R1_BAT.2
unnamed: MCP73831.1 (STAT), R1_BAT.1
unnamed: EPD_C1.1, J1.4
unnamed: MCP73831.5 (PROG), R2_BAT.2
unnamed: EPD_C2.1, J1.5
unnamed: D7.1 (CATHODE), R_CAPACITOR.1
unnamed: EPD_C8.1, J1.20
unnamed: EPD_C7.1, J1.19
unnamed: EPD_C6.1, J1.18
unnamed: EPD_C10.1, J1.22
unnamed: EPD_C12.1, J1.24
PREVGH: EPD_C9.1, J1.21
PREVGL: D4.2 (A), D5.1 (K), EPD_C11.1, J1.23
RESE: J1.3, Q3.2 (S), R3.1
RESE': R2.2, R3.2, SJ1.2
RESET: C5.1, IC1.1 (VOUT), RESET_BUTTON.3, RESET_BUTTON.4, R_RESET.2, U2.3 (EN)
RTC_RST: U2.16 (IO18), U3.4 (!RST)
RX: TP2.TP, U2.24 (RXD0/GPIO17)
SCK: D10.1, J1.13, J4.P5 (CLK), R6.1, TP8.TP, U1.6 (CLK), U2.6 (IO6)
SCL: J3.4, R2-PINH.1, SENSOR2.4 (SCK), U2.20 (IO22), U3.16 (SCL), U4.7 (SCL)
SDA: J3.3, R1_PINH.1, SENSOR2.3 (SDI), U2.19 (IO21), U3.15 (SDA), U4.8 (SDA)
SRC: C4.2, D5.2 (A), L1.1, Q3.3 (D)
SS_SD: D8.1, J4.P2 (CD/DAT3), R10.1, U2.4 (IO4)
TX: TP1.TP, U2.25 (TXD0/GPIO16)
USB_D+: D1.1 (I/O1_1), U2.14 (IO13)
USB_D-: D1.3 (I/O2_1), U2.13 (IO12)
VBAT: C2_BAT.1, MCP73831.3 (VBAT), Q1.3 (D), TP3.TP, U4.2 (CELL), U4.3 (VDD)
VBUS: C1_BAT.1, C4_USB.1, C5_USB.1, CHG_LED.A, D1.5 (VBUS), D2.2 (ANODE), MCP73831.4 (VIN), PFMF.050.1.2, Q1.1 (G), R1_PWRUSB.2, TP14.TP
VRTC: C8.1, C10_SUPERCAP.2, R_CAPACITOR.2, U3.14 (VBAT)
VUSB: J2.A4, J2.A9, J2.B4, J2.B9, PFMF.050.1.1

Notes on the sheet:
USB C connector & ESD protection
LDO Voltage Regulator
SD Card
Display Type Selector
E-Paper Drive Circuit
Li-Po Battery Charging Controller
ESP32 C6
E-Paper Display Header
EPD Power
Environmental Sensor BME688
BME688
RTC Module DS3231SN
Test Pads
Qwiic / Stemma QT
SPI ESD Protection Lines
External NOR Flash 64MB
Battery Charge Level
Voltage Supervisor + Reset & Boot / IO Button
OpenBook Schematic
drawn by: Gheorghe Razvan
DeskAssistant v19
DMG2305UX-7
SD0805S020S1R0

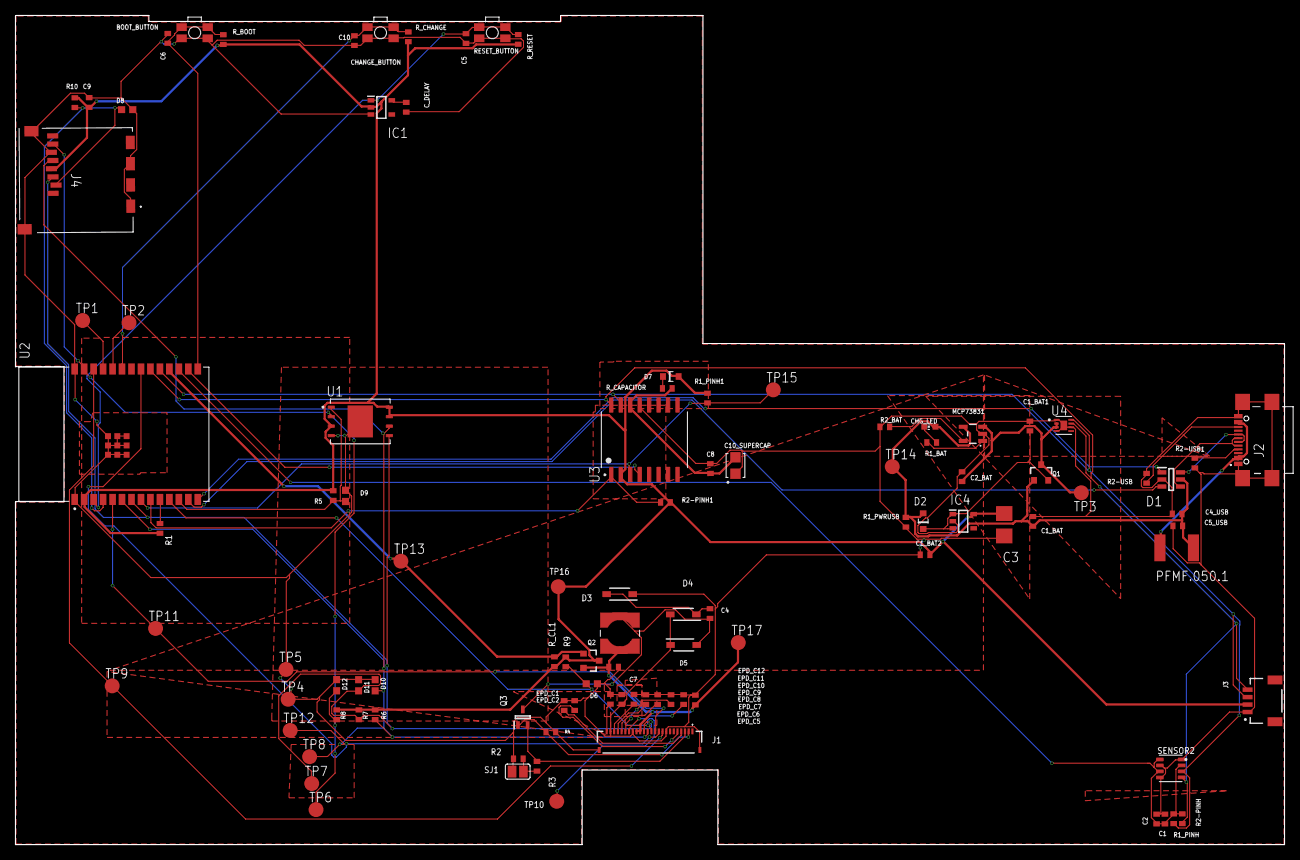
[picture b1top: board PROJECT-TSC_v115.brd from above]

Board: 2 copper layers, 170.2 x 111.2 mm, 103 parts (0 on the bottom side), 55 nets.

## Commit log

2025-04-05 Create LICENSE
2025-04-05 Create Hardware
2025-04-16 modificare_schematic dupa review

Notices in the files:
parts and their libraries:
COPYRIGHT: Copyright (C) 2024 Ultra Librarian. All rights reserved.
